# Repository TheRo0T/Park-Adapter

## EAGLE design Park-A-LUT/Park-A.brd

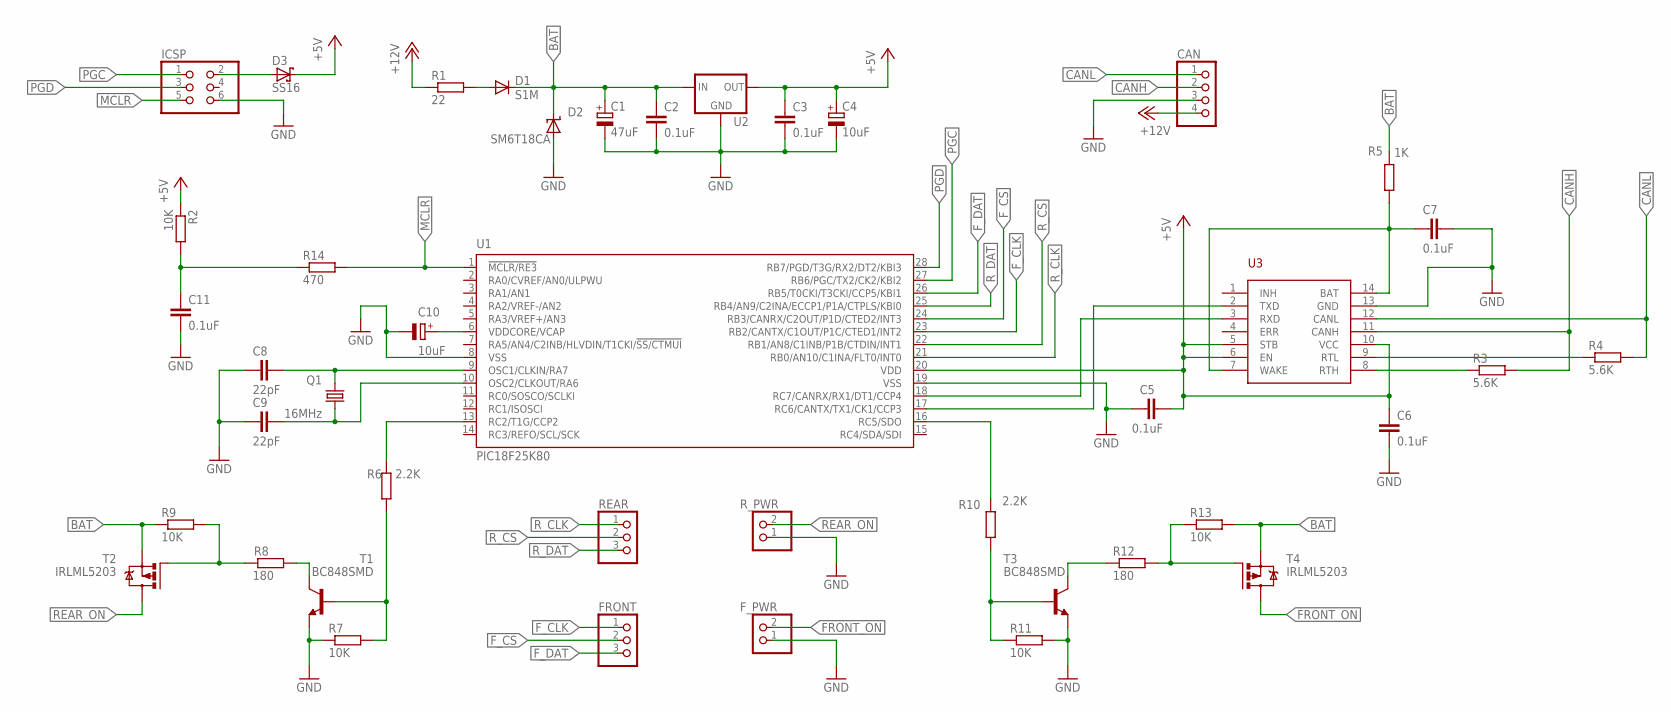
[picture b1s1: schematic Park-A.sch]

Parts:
C1: 47uF; 140CLH-0810
C2, C3, C5, C6, C7, C11: 0.1uF; C0805
C4: 10uF; 153CLV-0605
C8, C9: 22pF; C0805
C10: 10uF; SMC_A
CAN: PINHD-1X4; 1X04
D1: S1M; SMA
D2: SM6T18CA; SMBJ
D3: SS16; DO214AC
FRONT: PINHD-1X3; 1X03
F_PWR: PINHD-1X2; 1X02
ICSP: PINHD-2X3; 2X03
Q1: 16MHz; HC49/S
R1: 22; M1206
R2, R7, R9, R11, R13: 10K; R0805
R3, R4: 5.6K; R0805
R5: 1K; R0805
R6, R10: 2.2K; R0805
R8, R12: 180; R0805
R14: 470; R0805
REAR: PINHD-1X3; 1X03
R_PWR: PINHD-1X2; 1X02
T1, T3: BC848SMD; SOT23
T2, T4: IRLML5203; SOT23
U1: PIC18F25K80; SO28W
U2: 78M05; DPACK
U3: TJA1055T; SO-14W

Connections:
+5V: C3.1, C4.+, C5.1, C6.1, D3.C, R2.1, U1.20 (VDD), U2.3 (OUT), U3.5 (STB), U3.6 (EN), U3.10 (VCC)
+12V: CAN.4, R1.1
BAT: C1.+, C2.1, D1.C, D2.C, R5.2, R9.1, R13.2, T2.2 (S), T4.2 (S), U2.1 (IN)
CANH: CAN.2, R3.2, U3.11 (CANH)
CANL: CAN.1, R4.2, U3.12 (CANL)
FRONT_ON: F_PWR.2, T4.3 (D)
F_CLK: FRONT.1, U1.23 (RB2/CANTX/C1OUT/P1C/CTED1/INT2)
F_CS: FRONT.2, U1.24 (RB3/CANRX/C2OUT/P1D/CTED2/INT3)
F_DAT: FRONT.3, U1.26 (RB5/T0CKI/T3CKI/CCP5/KBI1)
GND: C1.-, C2.2, C3.2, C4.-, C5.2, C6.2, C7.2, C8.1, C9.1, C10.-, C11.2, CAN.3, D2.A, F_PWR.1, ICSP.6, R7.1, R11.2, R_PWR.1, T1.2 (E), T3.2 (E), U1.8 (VSS), U1.19 (VSS), U2.4 (GND), U3.13 (GND)
MCLR: ICSP.5, R14.2, U1.1 (!MCLR/RE3)
unnamed: D1.A, R1.2
unnamed: U1.17 (RC6/CANTX/TX1/CK1/CCP3), U3.2 (TXD)
unnamed: U1.18 (RC7/CANRX/RX1/DT1/CCP4), U3.3 (RXD)
unnamed: C11.1, R2.2, R14.1
unnamed: C8.2, Q1.1, U1.9 (OSC1/CLKIN/RA7)
unnamed: C7.1, R5.1, U3.7 (WAKE), U3.14 (BAT)
unnamed: C9.2, Q1.2, U1.10 (OSC2/CLKOUT/RA6)
unnamed: C10.+, U1.6 (VDDCORE/VCAP)
unnamed: R6.2, U1.13 (RC2/T1G/CCP2)
unnamed: R6.1, R7.2, T1.1 (B)
unnamed: R3.1, U3.8 (RTH)
unnamed: R4.1, U3.9 (RTL)
unnamed: R8.1, T1.3 (C)
unnamed: R8.2, R9.2, T2.1 (G)
unnamed: R10.2, U1.16 (RC5/SDO)
unnamed: R10.1, R11.1, T3.1 (B)
unnamed: R12.1, T3.3 (C)
unnamed: R12.2, R13.1, T4.1 (G)
unnamed: D3.A, ICSP.2
PGC: ICSP.1, U1.27 (RB6/PGC/TX2/CK2/KBI2)
PGD: ICSP.3, U1.28 (RB7/PGD/T3G/RX2/DT2/KBI3)
REAR_ON: R_PWR.2, T2.3 (D)
R_CLK: REAR.1, U1.21 (RB0/AN10/C1INA/FLT0/INT0)
R_CS: REAR.2, U1.22 (RB1/AN8/C1INB/P1B/CTDIN/INT1)
R_DAT: REAR.3, U1.25 (RB4/AN9/C2INA/ECCP1/P1A/CTPLS/KBI0)

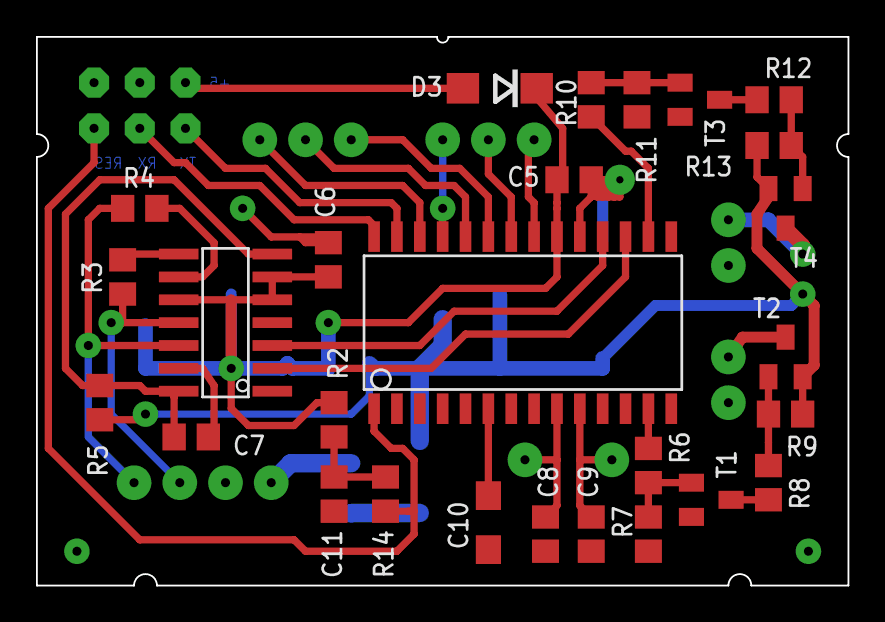
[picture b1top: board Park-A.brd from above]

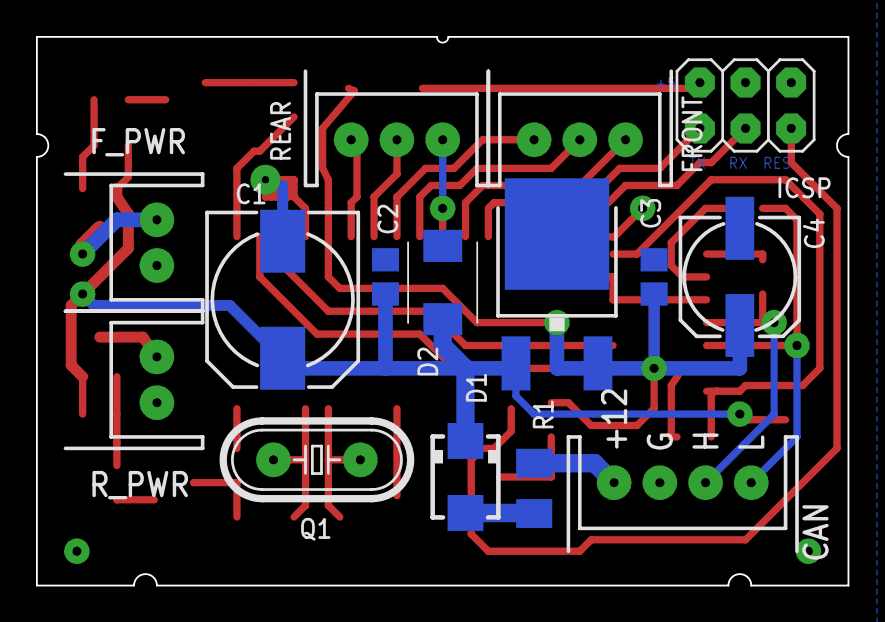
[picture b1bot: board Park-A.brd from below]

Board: 2 copper layers, 45.1 x 30.5 mm, 42 parts (15 on the bottom side), 36 nets.

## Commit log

2016-05-20 Add Eagle project
2016-08-31 Add ICSP
2016-09-01 Small fixes
